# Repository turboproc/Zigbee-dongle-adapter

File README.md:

# Introduction

The Zigbee dongle adapter allows for easy connection of the [Zigbee USB dongle](https://github.com/turboproc/Zigbee-USB-dongle) to the 
TI CC-DEVPACK-DEBUG debugger. This way the Zigbee USB dongle can be programmed through the CJTAG interface.

**WARNING: this is work in progress. Designs still need to be validaded on first prototypes.**

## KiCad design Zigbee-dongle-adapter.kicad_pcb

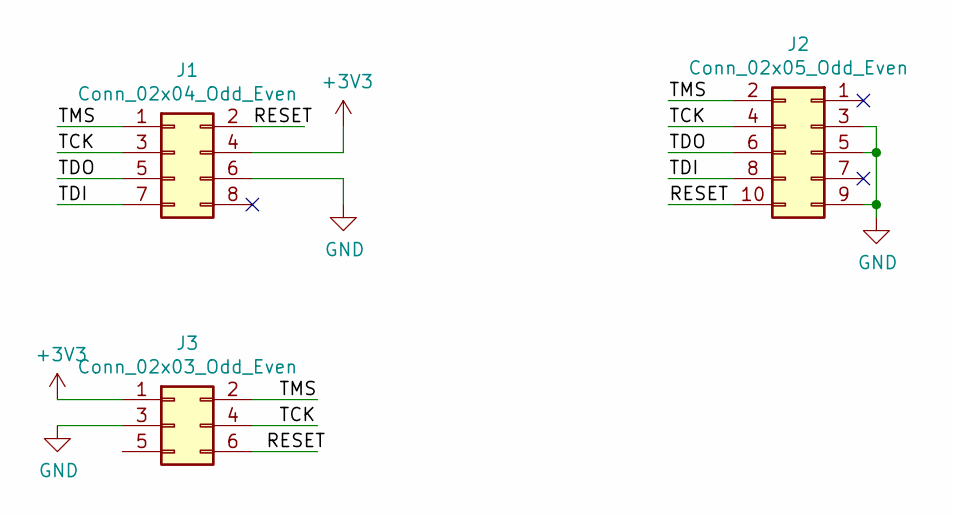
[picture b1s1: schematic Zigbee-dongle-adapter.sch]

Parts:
J1: Conn_02x04_Odd_Even; PinHeader_2x04_P2.54mm_Vertical
J2: Conn_02x05_Odd_Even; PinHeader_2x05_P1.27mm_Vertical
J3: Conn_02x03_Odd_Even; PinHeader_2x03_P2.54mm_Vertical

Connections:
+3V3: J1.4, J3.1
/RESET: J1.2, J2.10, J3.6
/TCK: J1.3, J2.4, J3.4
/TDI: J1.7, J2.8
/TDO: J1.5, J2.6
/TMS: J1.1, J2.2, J3.2
GND: J1.6, J2.3, J2.5, J2.9, J3.3

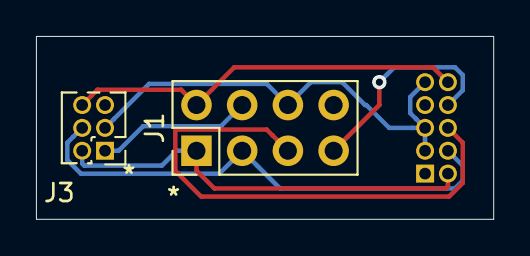
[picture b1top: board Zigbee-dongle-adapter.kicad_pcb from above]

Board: 2 copper layers, 25.4 x 10.2 mm, 3 parts (1 on the bottom side), 7 nets.

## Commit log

2020-04-02 Added pdf version of schema
